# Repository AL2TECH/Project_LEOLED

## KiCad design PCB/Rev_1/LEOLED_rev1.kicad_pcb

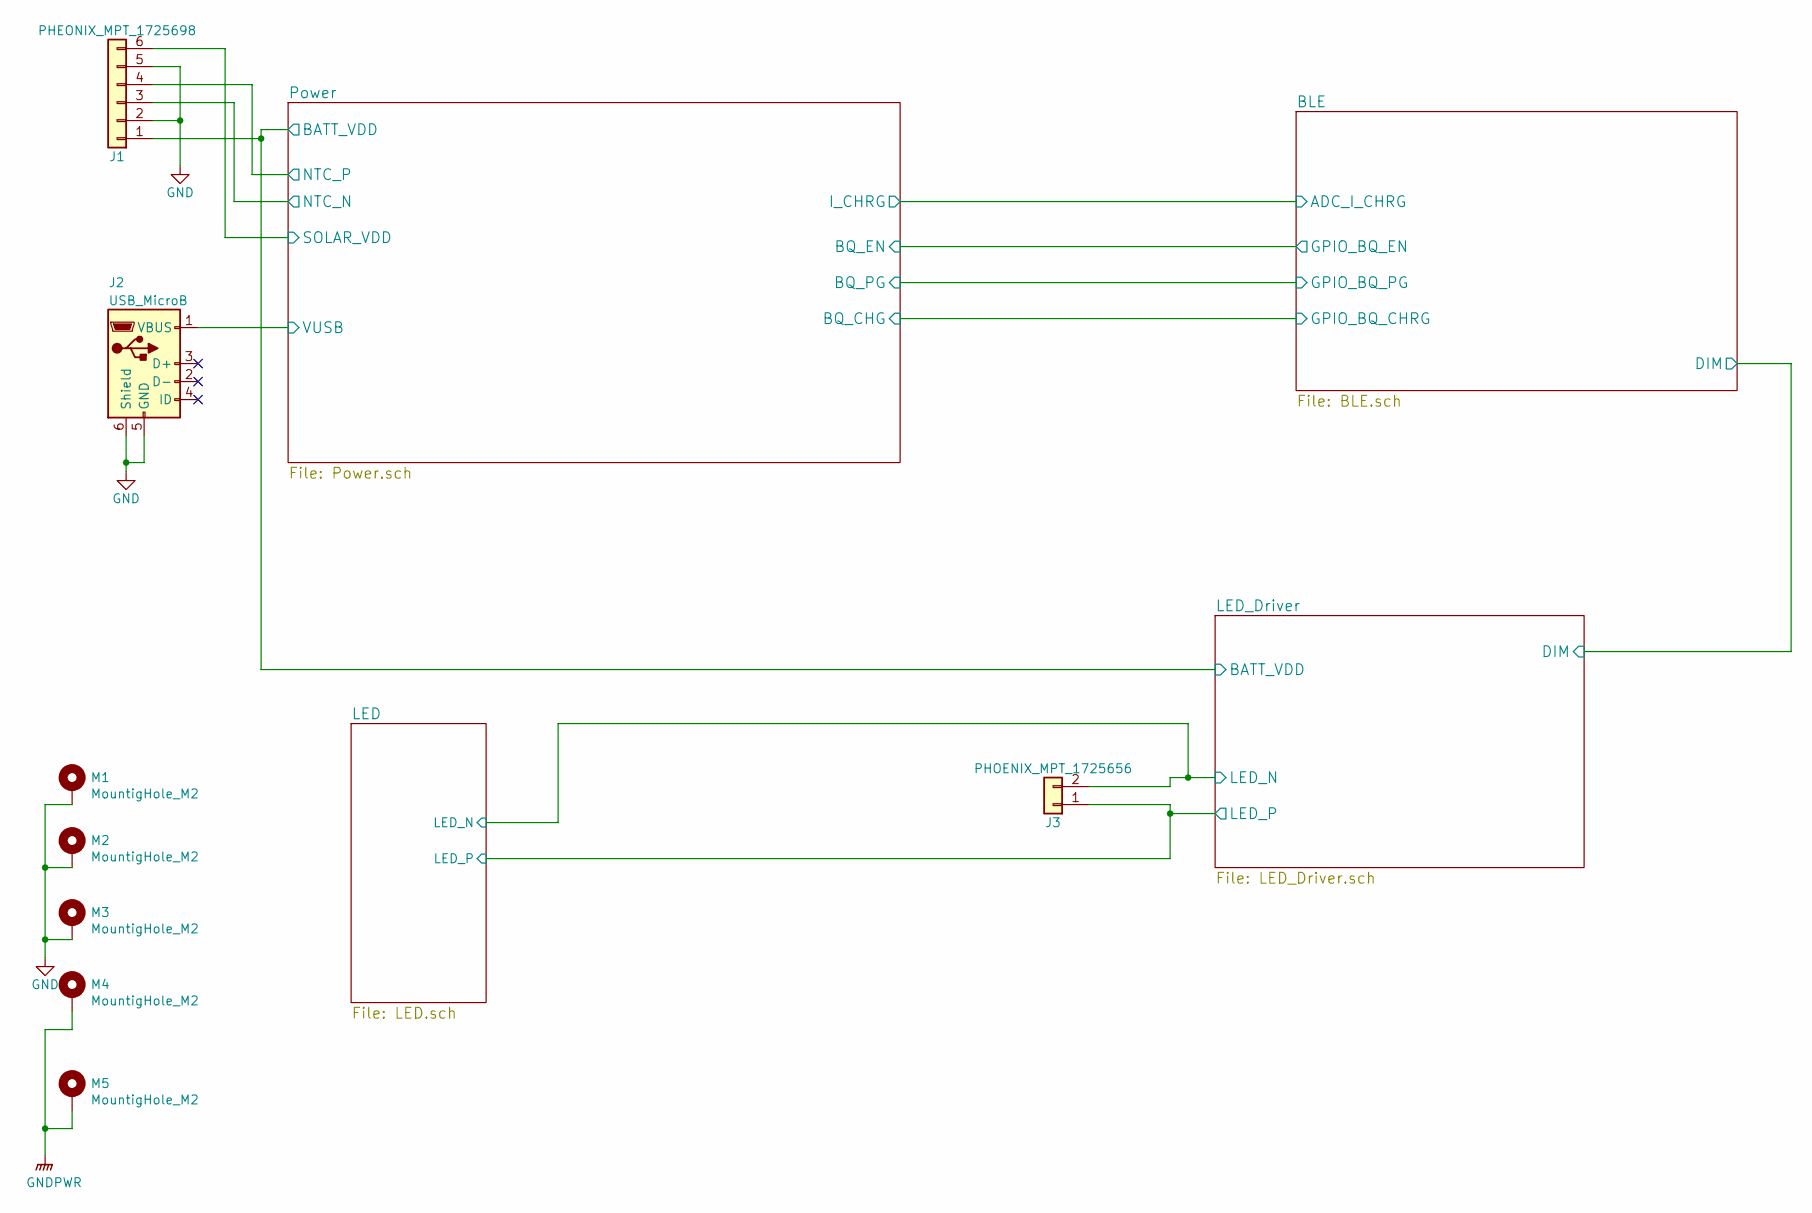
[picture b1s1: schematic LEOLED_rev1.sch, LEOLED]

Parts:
J1: PHEONIX_MPT_1725698; TerminalBlock_Pheonix_MPT-2.54mm_6pol; Rating 125V, 6A; Tolerance NA; Manufacturer PN 1725698
J2: USB_MicroB; USB_Micro-B_Molex-105017-0001; Rating NA; Tolerance NA; Manufacturer PN 1050170001
J3: PHOENIX_MPT_1725656; TerminalBlock_Pheonix_MPT-2.54mm_2pol; Rating 6A, 125V; Tolerance NA; Manufacturer PN 1725656
M1, M2, M3, M4, M5: MountigHole_M2; MountingHole_2.2mm_M2_ISO7380_Pad; Rating NA; Tolerance NA; Manufacturer PN NA

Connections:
/LED/LED_N: J3.2; also elsewhere on the board
/LED/LED_P: J3.1; also elsewhere on the board
/LED_Driver/BATT_VDD: J1.1; also elsewhere on the board
/Power/NTC_N: J1.3; also elsewhere on the board
/Power/NTC_P: J1.4; also elsewhere on the board
/Power/SOLAR_VDD: J1.6; also elsewhere on the board
/Power/VUSB: J2.1 (VBUS); also elsewhere on the board
GND: J1.2, J1.5, J2.5 (GND), J2.6 (Shield), M1.1, M2.1, M3.1; also elsewhere on the board
GNDPWR: M4.1, M5.1; also elsewhere on the board

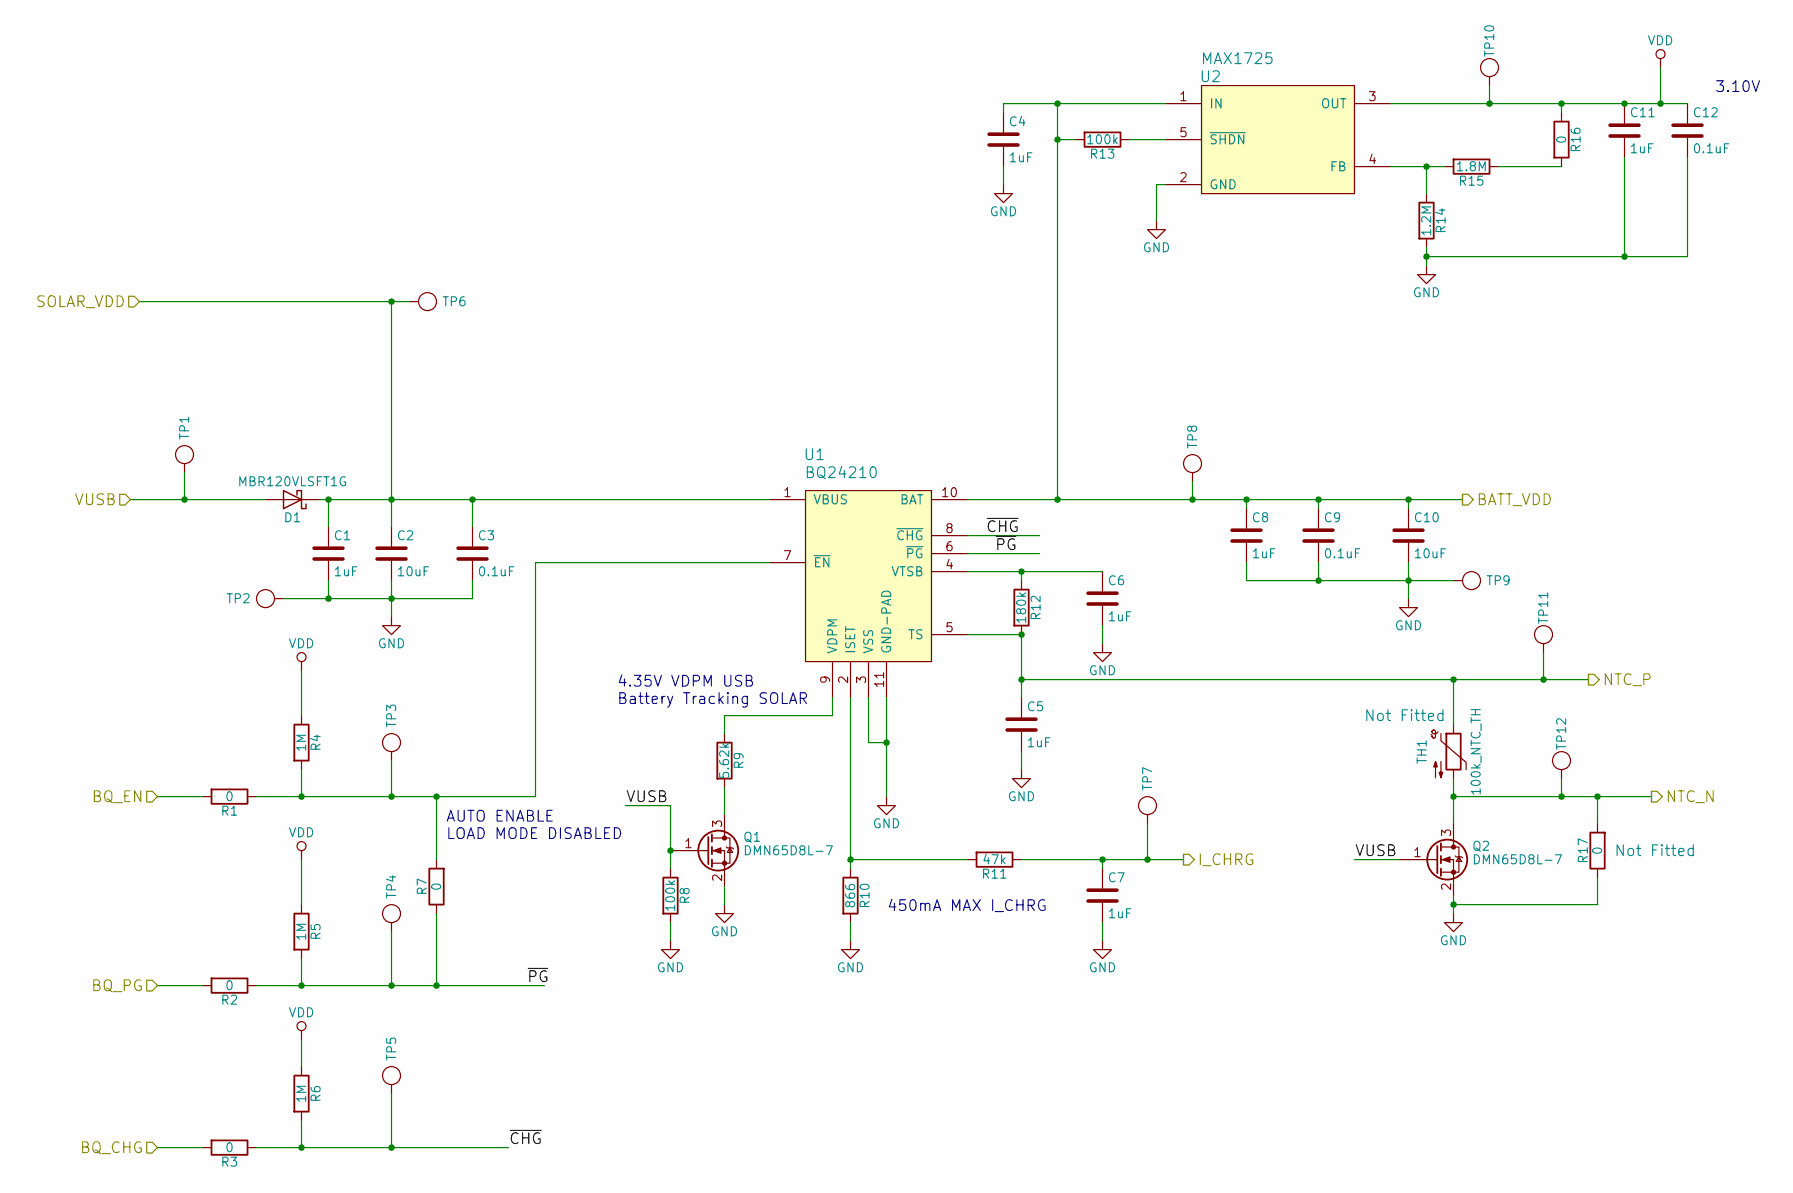
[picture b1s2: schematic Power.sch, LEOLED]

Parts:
C1, C4, C5, C6, C7, C8, C11: 1uF; C_0603_1608Metric; Rating 16V; Tolerance 20% X7R; Manufacturer PN GRM188R71C105MA12D
C2, C10: 10uF; C_1206_3216Metric; Rating 16V; Tolerance 10% X7R; Manufacturer PN CL31B106KOHZW6E
C3, C9, C12: 0.1uF; C_0603_1608Metric; Rating 16V; Tolerance 10% X7R; Manufacturer PN GRM188R71C104KA01D
D1: MBR120VLSFT1G; D_SOD-123FL; Rating 20V, 1A; Tolerance NA; Manufacturer PN MBR120VLSFT1G
Q1, Q2: DMN65D8L-7; SOT-23; Rating 60V, 310mA; Tolerance NA; Manufacturer PN DMN65D8L-7
R1, R2, R3, R7, R16, R17: 0; R_0603_1608Metric; Rating 0.1W; Tolerance 1%; Manufacturer PN CRG0603ZR
R4, R5, R6: 1M; R_0603_1608Metric; Rating 0.1W; Tolerance 1%; Manufacturer PN CRG0603F1M0
R8, R13: 100k; R_0603_1608Metric; Rating 0.1W; Tolerance 1%; Manufacturer PN CRG0603F100K
R9: 5.62k; R_0603_1608Metric; Rating 0.1W; Tolerance 1%; Manufacturer PN ERJ-3EKF5621V
R10: 866; R_0603_1608Metric; Rating 0.1W; Tolerance 1%; Manufacturer PN ERJ-3EKF8660V
R11: 47k; R_0603_1608Metric; Rating 0.1W; Tolerance 1%; Manufacturer PN CRCW060347K0FKEAC
R12: 180k; R_0603_1608Metric; Rating 0.1W; Tolerance 1%; Manufacturer PN CRCW0603180KFKEA
R14: 1.2M; R_0603_1608Metric; Rating 0.1W; Tolerance 1%; Manufacturer PN RC0603FR-071M2L
R15: 1.8M; R_0603_1608Metric; Rating 0.1W; Tolerance 1%; Manufacturer PN RC0603FR-071M8L
TH1: 100k_NTC_TH; R_0603_1608Metric; Rating NA; Tolerance 1%; Manufacturer PN NTCG164KF104FT1
TP1, TP2, TP3, TP4, TP5, TP6, TP7, TP8, TP9, TP10, TP11, TP12: Test_Point; TestPoint_Pad_D1.5mm; Rating NA; Tolerance NA; Manufacturer PN NA
U1: BQ24210; WSON-10-1EP_2x3mm_Pitch0.5mm_ThermalVias; Rating 7V; Tolerance NA; Manufacturer PN BQ24210DQCT
U2: MAX1725; SOT-23-5; Rating 12V; Tolerance NA; Manufacturer PN MAX1725EUK+T

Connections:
/BLE/ADC_I_CHRG: C7.1, R11.1, TP7.1; also elsewhere on the board
/LED_Driver/BATT_VDD: C4.1, C8.1, C9.1, C10.1, R13.2, TP8.1, U1.10 (BAT), U2.1 (IN); also elsewhere on the board
/Power/BQ_CHG: R3.2; also elsewhere on the board
/Power/BQ_EN: R1.2; also elsewhere on the board
/Power/BQ_PG: R2.2; also elsewhere on the board
/Power/NTC_N: Q2.3 (D), R17.2, TH1.2, TP12.1; also elsewhere on the board
/Power/NTC_P: C5.1, R12.2, TH1.1, TP11.1, U1.5 (TS); also elsewhere on the board
/Power/SOLAR_VDD: C1.1, C2.1, C3.1, D1.1 (K), TP6.1, U1.1 (VBUS); also elsewhere on the board
/Power/VUSB: D1.2 (A), Q1.1 (G), Q2.1 (G), R8.1, TP1.1; also elsewhere on the board
/Power/~CHG: R3.1, R6.2, TP5.1, U1.8 (~CHG)
/Power/~PG: R2.1, R5.2, R7.1, TP4.1, U1.6 (~PG)
GND: C1.2, C2.2, C3.2, C4.2, C5.2, C6.2, C7.2, C8.2, C9.2, C10.2, C11.2, C12.2, Q1.2 (S), Q2.2 (S), R8.2, R10.2, R14.2, R17.1, TP2.1, TP9.1, U1.3 (VSS), U1.11 (GND-PAD), U2.2 (GND); also elsewhere on the board
unnamed: C6.1, R12.1, U1.4 (VTSB)
unnamed: Q1.3 (D), R9.2
unnamed: R1.1, R4.2, R7.2, TP3.1, U1.7 (~EN)
unnamed: R9.1, U1.9 (VDPM)
unnamed: R10.1, R11.2, U1.2 (ISET)
unnamed: R13.1, U2.5 (~SHDN)
unnamed: R14.1, R15.2, U2.4 (FB)
unnamed: R15.1, R16.2
VDD: C11.1, C12.1, R4.1, R5.1, R6.1, R16.1, TP10.1, U2.3 (OUT); also elsewhere on the board

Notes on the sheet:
450mA MAX I_CHRG
4.35V VDPM USB Battery Tracking SOLAR
AUTO ENABLE LOAD MODE DISABLED
3.10V

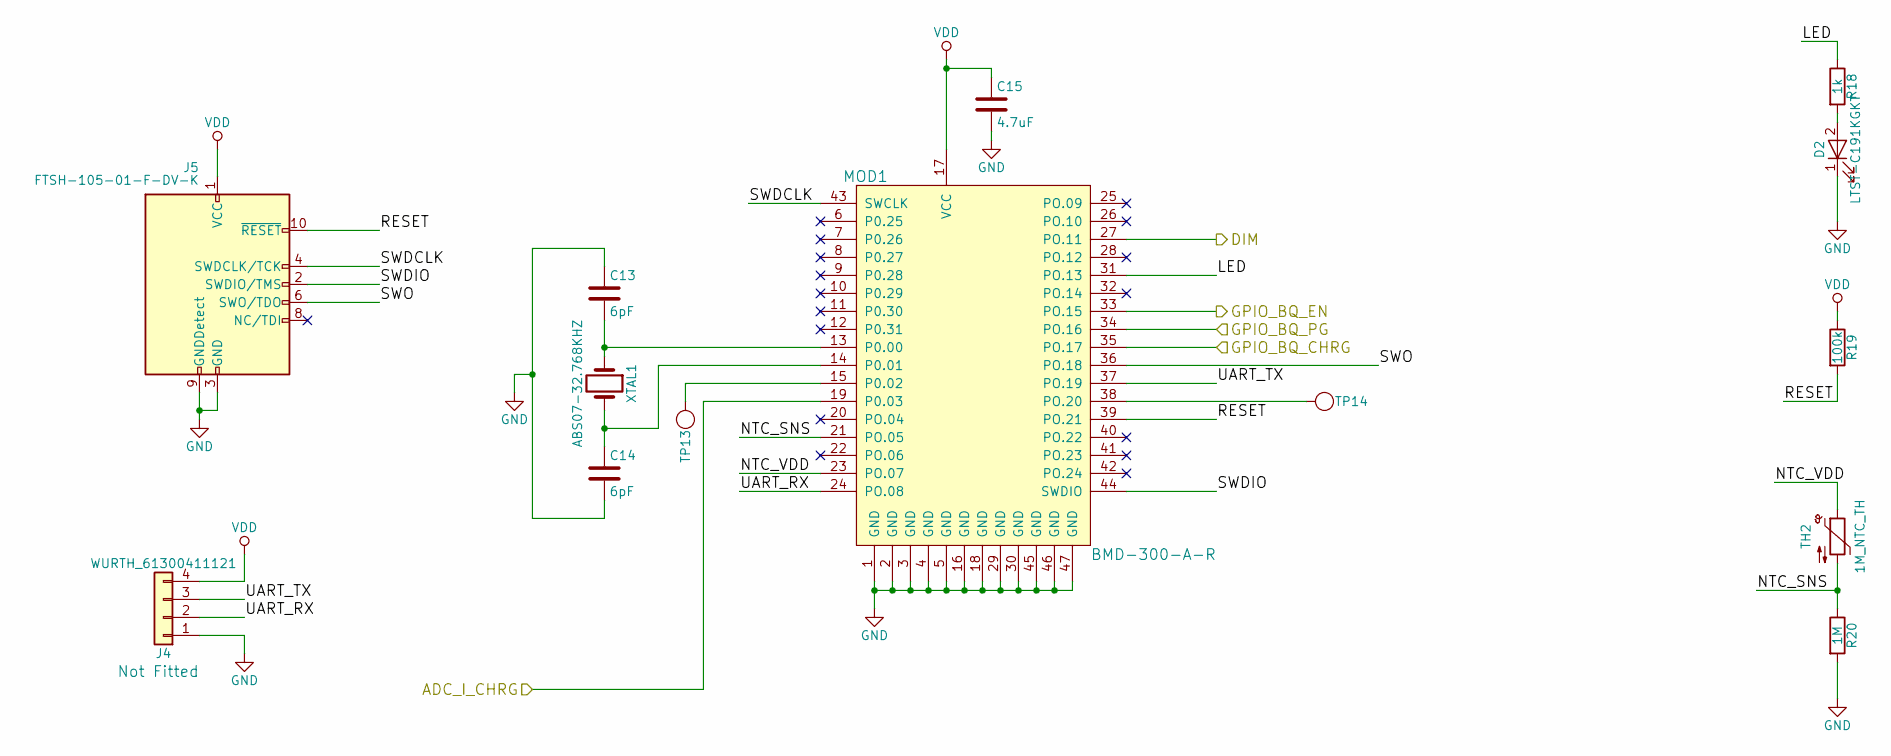
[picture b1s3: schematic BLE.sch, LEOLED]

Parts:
C13, C14: 6pF; C_0402_1005Metric; Rating 50V; Tolerance ±0.5pF; Manufacturer PN GRM1555C1H6R0DA01D
C15: 4.7uF; C_0603_1608Metric; Rating 16V; Tolerance 10% X5R; Manufacturer PN CL10A475KO8NNNC
D2: LTST-C191KGKT; LED_0603_1608Metric; Rating 20mA; Tolerance NA; Manufacturer PN LTST-C191KGKT
J4: WURTH_61300411121; Pin_Header_Straight_1x04_Pitch2.54mm; Rating NA; Tolerance NA; Manufacturer PN 61300411121
J5: FTSH-105-01-F-DV-K; Pin_Header_Straight_2x05_Pitch1.27mm_SMD; Rating NA; Tolerance NA; Manufacturer PN FTSH-105-01-F-DV-K
MOD1: BMD-300-A-R; BLE_Rigado_BMD-300; Rating 1.7V to 3V; Tolerance NA; Manufacturer PN BMD-300-A-R
R18: 1k; R_0603_1608Metric; Rating 0.1W; Tolerance 1%; Manufacturer PN CRG0603F1K0
R19: 100k; R_0603_1608Metric; Rating 0.1W; Tolerance 1%; Manufacturer PN CRG0603F100K
R20: 1M; R_0603_1608Metric; Rating 0.1W; Tolerance 1%; Manufacturer PN CRG0603F1M0
TH2: 1M_NTC_TH; R_0603_1608Metric; Rating 0.1W; Tolerance 3%, B25/50 4661K; Manufacturer PN NTCG164QH105HT1
TP13, TP14: Test_Point; TestPoint_Pad_D1.5mm; Rating NA; Tolerance NA; Manufacturer PN NA
XTAL1: ABS07-32.768KHZ; ABS07-32.768KHZ-7-T; Rating NA; Tolerance 20ppm; Manufacturer PN ABS07-32.768KHZ-7-T

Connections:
/BLE/ADC_I_CHRG: MOD1.19 (P0.03); also elsewhere on the board
/BLE/DIM: MOD1.27 (PO.11); also elsewhere on the board
/BLE/LED: MOD1.31 (PO.13), R18.1
/BLE/NTC_SNS: MOD1.21 (PO.05), R20.1, TH2.2
/BLE/NTC_VDD: MOD1.23 (PO.07), TH2.1
/BLE/RESET: J5.10 (~RESET~), MOD1.39 (PO.21), R19.2
/BLE/SWDCLK: J5.4 (SWDCLK/TCK), MOD1.43 (SWCLK)
/BLE/SWDIO: J5.2 (SWDIO/TMS), MOD1.44 (SWDIO)
/BLE/SWO: J5.6 (SWO/TDO), MOD1.36 (PO.18)
/BLE/UART_RX: J4.2, MOD1.24 (PO.08)
/BLE/UART_TX: J4.3, MOD1.37 (PO.19)
/Power/BQ_CHG: MOD1.35 (PO.17); also elsewhere on the board
/Power/BQ_EN: MOD1.33 (PO.15); also elsewhere on the board
/Power/BQ_PG: MOD1.34 (PO.16); also elsewhere on the board
GND: C13.1, C14.2, C15.2, D2.1 (K), J4.1, J5.3 (GND), J5.5 (GND), J5.9 (GNDDetect), MOD1.1 (GND), MOD1.2 (GND), MOD1.3 (GND), MOD1.4 (GND), MOD1.5 (GND), MOD1.16 (GND), MOD1.18 (GND), MOD1.29 (GND), MOD1.30 (GND), MOD1.45 (GND), MOD1.46 (GND), MOD1.47 (GND), R20.2; also elsewhere on the board
unnamed: C13.2, MOD1.13 (P0.00), XTAL1.1
unnamed: C14.1, MOD1.14 (P0.01), XTAL1.2
unnamed: D2.2 (A), R18.2
unnamed: MOD1.15 (P0.02), TP13.1
unnamed: MOD1.38 (PO.20), TP14.1
VDD: C15.1, J4.4, J5.1 (VCC), MOD1.17 (VCC), R19.1; also elsewhere on the board

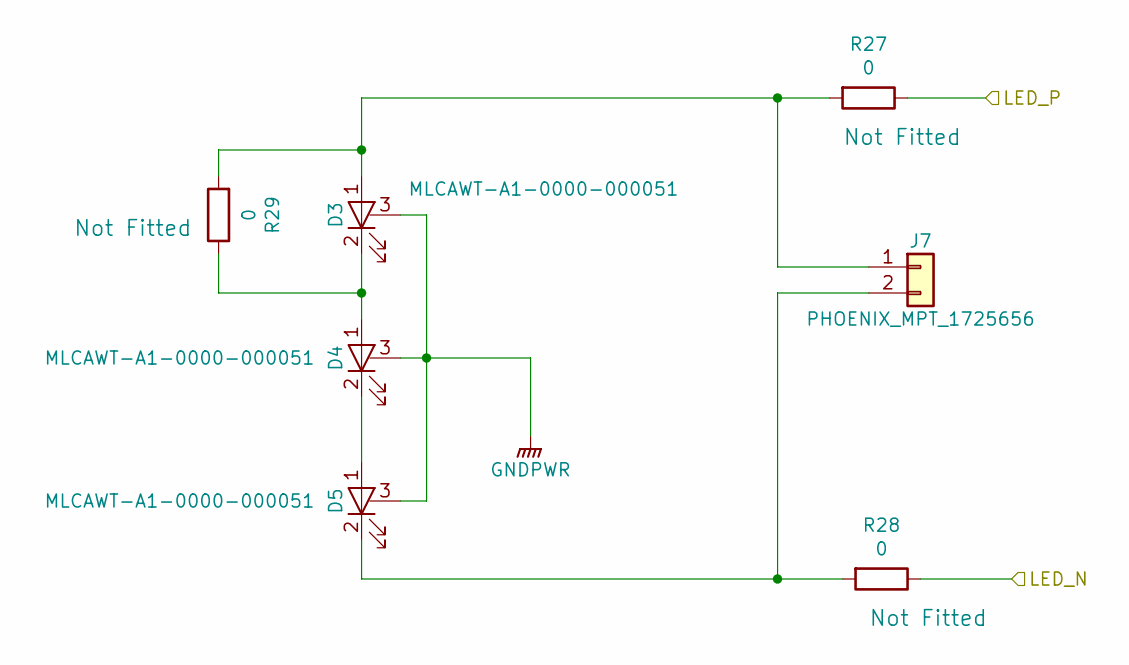
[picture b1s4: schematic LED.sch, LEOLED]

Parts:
D3, D4, D5: MLCAWT-A1-0000-000051; Cree_MLC; Rating 300mW; Tolerance NA; Manufacturer PN MLCAWT-A1-0000-000051
J7: PHOENIX_MPT_1725656; TerminalBlock_Pheonix_MPT-2.54mm_2pol; Rating 6A, 125V; Tolerance NA; Manufacturer PN 1725656
R27, R28, R29: 0; R_0805_2012Metric; Rating 0.125W; Tolerance NA; Manufacturer PN ERJ-6GEY0R00V

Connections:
/LED/LED_N: R28.1; also elsewhere on the board
/LED/LED_P: R27.1; also elsewhere on the board
GNDPWR: D3.3 (HS), D4.3 (HS), D5.3 (HS); also elsewhere on the board
unnamed: D3.1 (A), J7.1, R27.2, R29.2
unnamed: D3.2 (K), D4.1 (A), R29.1
unnamed: D4.2 (K), D5.1 (A)
unnamed: D5.2 (K), J7.2, R28.2

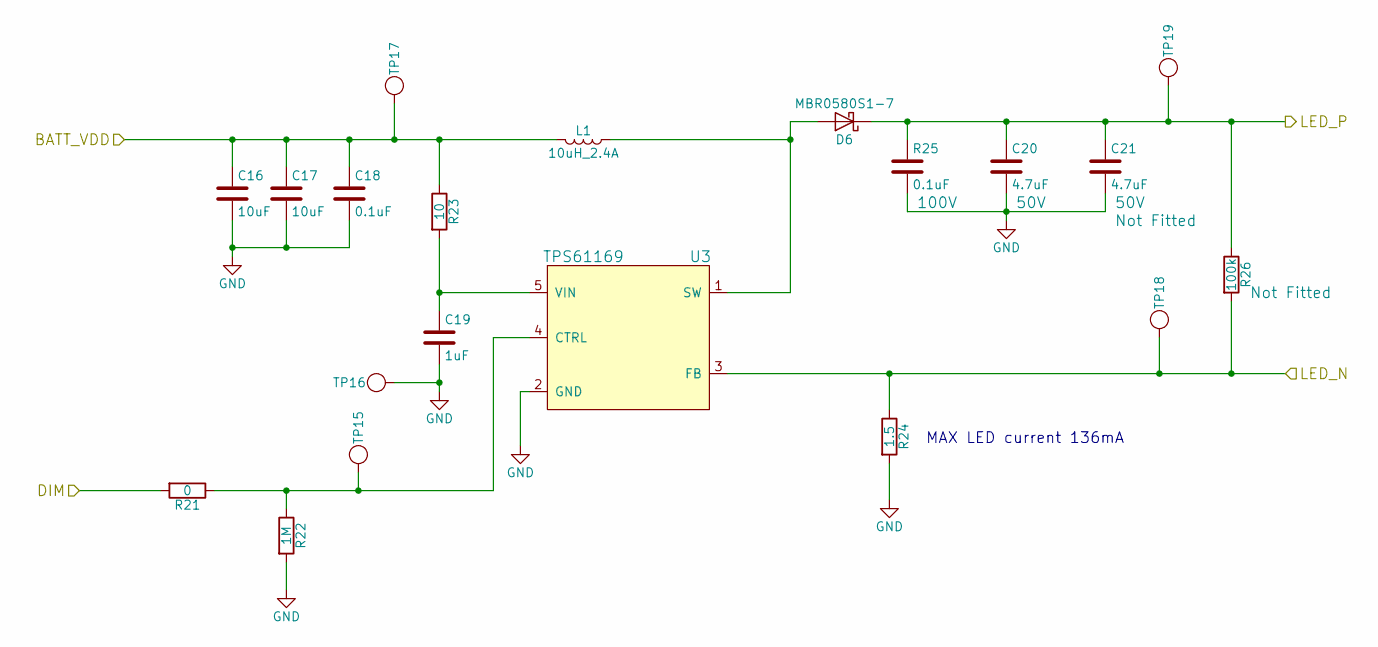
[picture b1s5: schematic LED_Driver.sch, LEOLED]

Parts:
C16, C17: 10uF; C_1206_3216Metric; Rating 16V; Tolerance 10% X7R; Manufacturer PN CL31B106KOHZW6E
C18: 0.1uF; C_0603_1608Metric; Rating 16V; Tolerance 10% X7R; Manufacturer PN GRM188R71C104KA01D
C19: 1uF; C_0603_1608Metric; Rating 16V; Tolerance 20% X7R; Manufacturer PN GRM188R71C105MA12D
C20, C21: 4.7uF; C_1206_3216Metric; Rating 50V; Tolerance X5R; Manufacturer PN CL31A475KB9LNNC
D6: MBR0580S1-7; D_SOD-123; Rating 500mA, 80V; Tolerance NA; Manufacturer PN MBR0580S1-7
L1: 10uH_2.4A; L_Wurth_5030; Rating 2.4A; Tolerance 20%; Manufacturer PN 74437336100
R21: 0; R_0603_1608Metric; Rating 0.1W; Tolerance 1%; Manufacturer PN CRG0603ZR
R22: 1M; R_0603_1608Metric; Rating 0.1W; Tolerance 1%; Manufacturer PN CRG0603F1M0
R23: 10; R_0603_1608Metric; Rating 0.1W; Tolerance 1%; Manufacturer PN AC0603FR-0710RL
R24: 1.5; R_0805_2012Metric; Rating 0.125W; Tolerance 1%; Manufacturer PN RC0805FR-071R5L
R25: 0.1uF; C_0805_2012Metric; Rating 100V; Tolerance 10%; Manufacturer PN GCM21BR72A104KA37L
R26: 100k; R_0603_1608Metric; Rating 0.1W; Tolerance 1%; Manufacturer PN CRG0603F100K
TP15, TP16, TP17, TP18, TP19: Test_Point; TestPoint_Pad_D1.5mm; Rating NA; Tolerance NA; Manufacturer PN NA
U3: TPS61169; TI_SC-70-5; Rating NA; Tolerance NA; Manufacturer PN TPS61169DCKR

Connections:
/BLE/DIM: R21.2; also elsewhere on the board
/LED/LED_N: R24.1, R26.2, TP18.1, U3.3 (FB); also elsewhere on the board
/LED/LED_P: C20.1, C21.1, D6.1 (K), R25.1, R26.1, TP19.1; also elsewhere on the board
/LED_Driver/BATT_VDD: C16.1, C17.1, C18.1, L1.2, R23.1, TP17.1; also elsewhere on the board
GND: C16.2, C17.2, C18.2, C19.2, C20.2, C21.2, R22.2, R24.2, R25.2, TP16.1, U3.2 (GND); also elsewhere on the board
unnamed: C19.1, R23.2, U3.5 (VIN)
unnamed: D6.2 (A), L1.1, U3.1 (SW)
unnamed: R21.1, R22.1, TP15.1, U3.4 (CTRL)

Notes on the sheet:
MAX LED current 136mA

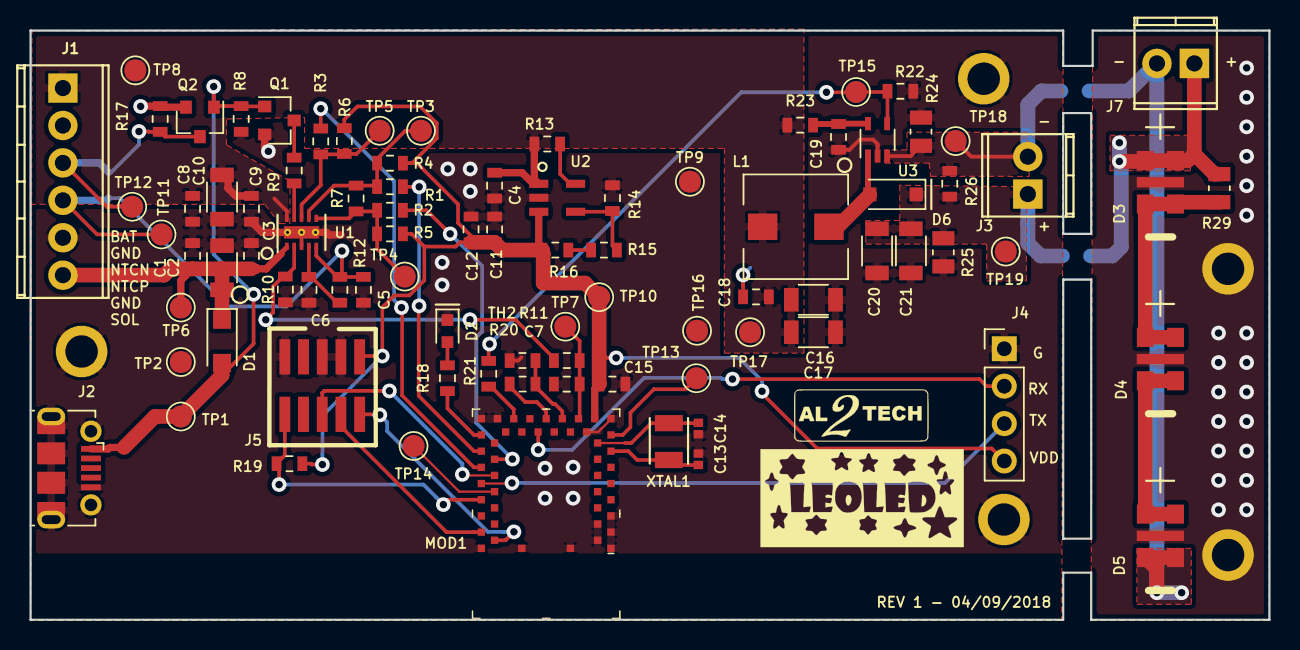
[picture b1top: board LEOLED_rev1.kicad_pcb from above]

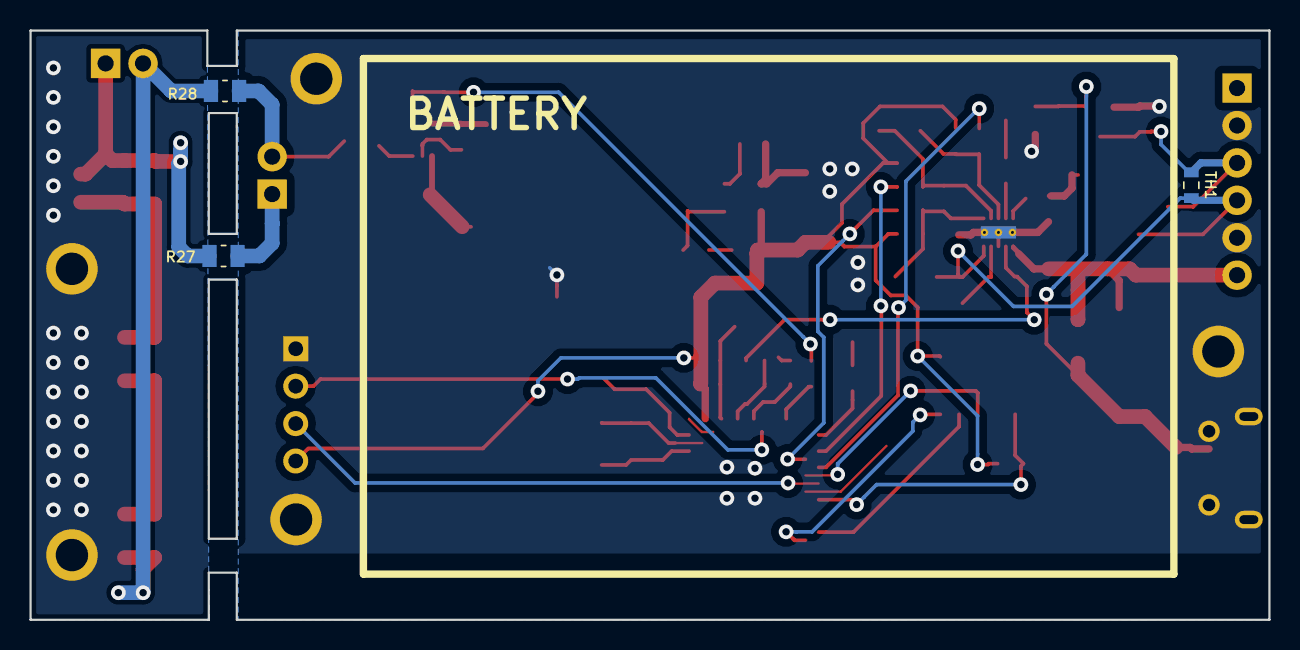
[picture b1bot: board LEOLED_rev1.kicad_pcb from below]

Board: 2 copper layers, 84.1 x 40.0 mm, 96 parts (3 on the bottom side), 46 nets.

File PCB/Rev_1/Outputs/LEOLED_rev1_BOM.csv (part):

"Source:","C:\Users\andrea.longobardi\OneDrive - maximintegrated.onmicrosoft.com\WORK\PERSONAL\AL2TECH\LEOLED\PCB\Rev_1\LEOLED_rev1.sch"
"Date:","6/25/2018 2:30:03 PM"
"Tool:","Eeschema (5.0.0-rc2-199-gf785d2749)"
"Generator:","C:\github_repo\Utilities\KiCad\KiCad_BOM_Generator/kicad_bom_generator.py"
"Component Count:","70"

"Individual Components:"

"Item","Qty","Reference(s)","Value","Description","Footprint","Datasheet","Rating","Tolerance","Manufacturer","Manufacturer PN","Supplier","Supplier PN","Supplier Link","Assembly Option"
"","","C1","1uF","	 1uF ±20% 16V Ceramic Capacitor X7R 0603 (1608 Metric)","Ceramic_Capacitor_SMD:C_0603_1608Metric","http://search.murata.co.jp/Ceramy/image/img/A01X/G101/ENG/GR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","16V","20% X7R ","Murata Electronics North America","GRM188R71C105MA12D","Digy-Key","490-6424-1-ND","https://www.digikey.com/product-detail/en/murata-electronics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","Fitted"
"","","C2","10uF","10µF ±10% 16V Ceramic Capacitor X7R 1206 (3216 Metric)","Ceramic_Capacitor_SMD:C_1206_3216Metric","http://www.samsungsem.com/kr/support/product-search/mlcc/CL3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","16V","10% X7R","Samsung Electro-Mechanics","CL31B106KOHZW6E","Digy-Key","1276-7032-1-ND","https://www.digikey.com/product-detail/en/samsung-electro-me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","Fitted"
"","","C3","0.1uF","	0.1uF ±10% 16V Ceramic Capacitor X7R 0603 (1608 Metric)","Ceramic_Capacitor_SMD:C_0603_1608Metric","http://search.murata.co.jp/Ceramy/image/img/A01X/G101/ENG/GR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","16V","10% X7R ","Murata Electronics North America","GRM188R71C104KA01D","Digy-Key","490-1532-1-ND","https://www.digikey.com/product-detail/en/murata-electronics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","Fitted"
"","","C4","1uF","	 1uF ±20% 16V Ceramic Capacitor X7R 0603 (1608 Metric)","Ceramic_Capacitor_SMD:C_0603_1608Metric","http://search.murata.co.jp/Ceramy/image/img/A01X/G101/ENG/GR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","16V","20% X7R ","Murata Electronics North America","GRM188R71C105MA12D","Digy-Key","490-6424-1-ND","https://www.digikey.com/product-detail/en/murata-electronics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","Fitted"
"","","C5","1uF","	 1uF ±20% 16V Ceramic Capacitor X7R 0603 (1608 Metric)","Ceramic_Capacitor_SMD:C_0603_1608Metric","http://search.murata.co.jp/Ceramy/image/img/A01X/G101/ENG/GR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","16V","20% X7R ","Murata Electronics North America","GRM188R71C105MA12D","Digy-Key","490-6424-1-ND","https://www.digikey.com/product-detail/en/murata-electronics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","Fitted"
"","","C6","1uF","	 1uF ±20% 16V Ceramic Capacitor X7R 0603 (1608 Metric)","Ceramic_Capacitor_SMD:C_0603_1608Metric","http://search.murata.co.jp/Ceramy/image/img/A01X/G101/ENG/GR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","16V","20% X7R ","Murata Electronics North America","GRM188R71C105MA12D","Digy-Key","490-6424-1-ND","https://www.digikey.com/product-detail/en/murata-electronics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","Fitted"
"","","C7","1uF","	 1uF ±20% 16V Ceramic Capacitor X7R 0603 (1608 Metric)","Ceramic_Capacitor_SMD:C_0603_1608Metric","http://search.murata.co.jp/Ceramy/image/img/A01X/G101/ENG/GR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","16V","20% X7R ","Murata Electronics North America","GRM188R71C105MA12D","Digy-Key","490-6424-1-ND","https://www.digikey.com/product-detail/en/murata-electronics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","Fitted"
"","","C8","1uF","	 1uF ±20% 16V Ceramic Capacitor X7R 0603 (1608 Metric)","Ceramic_Capacitor_SMD:C_0603_1608Metric","http://search.murata.co.jp/Ceramy/image/img/A01X/G101/ENG/GR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","16V","20% X7R ","Murata Electronics North America","GRM188R71C105MA12D","Digy-Key","490-6424-1-ND","https://www.digikey.com/product-detail/en/murata-electronics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","Fitted"
"","","C9","0.1uF","	0.1uF ±10% 16V Ceramic Capacitor X7R 0603 (1608 Metric)","Ceramic_Capacitor_SMD:C_0603_1608Metric","http://search.murata.co.jp/Ceramy/image/img/A01X/G101/ENG/GR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","16V","10% X7R ","Murata Electronics North America","GRM188R71C104KA01D","Digy-Key","490-1532-1-ND","https://www.digikey.com/product-detail/en/murata-electronics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","Fitted"
"","","C10","10uF","10µF ±10% 16V Ceramic Capacitor X7R 1206 (3216 Metric)","Ceramic_Capacitor_SMD:C_1206_3216Metric","http://www.samsungsem.com/kr/support/product-search/mlcc/CL3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","16V","10% X7R","Samsung Electro-Mechanics","CL31B106KOHZW6E","Digy-Key","1276-7032-1-ND","https://www.digikey.com/product-detail/en/samsung-electro-me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","Fitted"
"","","C11","1uF","	 1uF ±20% 16V Ceramic Capacitor X7R 0603 (1608 Metric)","Ceramic_Capacitor_SMD:C_0603_1608Metric","http://search.murata.co.jp/Ceramy/image/img/A01X/G101/ENG/GR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","16V","20% X7R ","Murata Electronics North America","GRM188R71C105MA12D","Digy-Key","490-6424-1-ND","https://www.digikey.com/product-detail/en/murata-electronics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","Fitted"
"","","C12","0.1uF","	0.1uF ±10% 16V Ceramic Capacitor X7R 0603 (1608 Metric)","Ceramic_Capacitor_SMD:C_0603_1608Metric","http://search.murata.co.jp/Ceramy/image/img/A01X/G101/ENG/GR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","16V","10% X7R ","Murata Electronics North America","GRM188R71C104KA01D","Digy-Key","490-1532-1-ND","https://www.digikey.com/product-detail/en/murata-electronics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","Fitted"
"","","C13","6pF","6pF ±0.5pF 50V Ceramic Capacitor C0G, NP0 0402","Ceramic_Capacitor_SMD:C_0402_1005Metric","http://search.murata.co.jp/Ceramy/image/img/A01X/G101/ENG/GR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","50V","±0.5pF","Murata Electronics North America","GRM1555C1H6R0DA01D","Digy-Key","490-5877-1-ND","https://www.digikey.com/products/en?keywords=490-5877-1-ND","Fitted"
"","","C14","6pF","6pF ±0.5pF 50V Ceramic Capacitor C0G, NP0 0402","Ceramic_Capacitor_SMD:C_0402_1005Metric","http://search.murata.co.jp/Ceramy/image/img/A01X/G101/ENG/GR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","50V","±0.5pF","Murata Electronics North America","GRM1555C1H6R0DA01D","Digy-Key","490-5877-1-ND","https://www.digikey.com/products/en?keywords=490-5877-1-ND","Fitted"
"","","C15","4.7uF","	 4.7uF ±10% 16V Ceramic Capacitor X5R 0603 (1608 Metric)","Ceramic_Capacitor_SMD:C_0603_1608Metric","http://www.samsungsem.com/kr/front/downloadcms.do?path=/kr/s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","16V","10% X5R","Samsung Electro-Mechanics","CL10A475KO8NNNC","Digy-Key","1276-1784-1-ND","https://www.digikey.com/product-detail/en/samsung-electro-me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","Fitted"
"","","C16","10uF","10µF ±10% 16V Ceramic Capacitor X7R 1206 (3216 Metric)","Ceramic_Capacitor_SMD:C_1206_3216Metric","http://www.samsungsem.com/kr/support/product-search/mlcc/CL3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","16V","10% X7R","Samsung Electro-Mechanics","CL31B106KOHZW6E","Digy-Key","1276-7032-1-ND","https://www.digikey.com/product-detail/en/samsung-electro-me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","Fitted"
"","","C17","10uF","10µF ±10% 16V Ceramic Capacitor X7R 1206 (3216 Metric)","Ceramic_Capacitor_SMD:C_1206_3216Metric","http://www.samsungsem.com/kr/support/product-search/mlcc/CL3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","16V","10% X7R","Samsung Electro-Mechanics","CL31B106KOHZW6E","Digy-Key","1276-7032-1-ND","https://www.digikey.com/product-detail/en/samsung-electro-me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","Fitted"
"","","C18","0.1uF","	0.1uF ±10% 16V Ceramic Capacitor X7R 0603 (1608 Metric)","Ceramic_Capacitor_SMD:C_0603_1608Metric","http://search.murata.co.jp/Ceramy/image/img/A01X/G101/ENG/GR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","16V","10% X7R ","Murata Electronics North America","GRM188R71C104KA01D","Digy-Key","490-1532-1-ND","https://www.digikey.com/product-detail/en/murata-electronics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","Fitted"
"","","C19","1uF","	 1uF ±20% 16V Ceramic Capacitor X7R 0603 (1608 Metric)","Ceramic_Capacitor_SMD:C_0603_1608Metric","http://search.murata.co.jp/Ceramy/image/img/A01X/G101/ENG/GR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","16V","20% X7R ","Murata Electronics North America","GRM188R71C105MA12D","Digy-Key","490-6424-1-ND","https://www.digikey.com/product-detail/en/murata-electronics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","Fitted"
"","","C20","4.7uF","4.7µF ±10% 50V Ceramic Capacitor X5R 1206 (3216 Metric)","Ceramic_Capacitor_SMD:C_1206_3216Metric","http://www.samsungsem.com/kr/support/product-search/mlcc/CL3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","50V","X5R","Samsung Electro-Mechanics","CL31A475KB9LNNC","Digy-Key","1276-2731-2-ND","https://www.digikey.com/product-detail/en/samsung-electro-me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","Fitted"
"","","C21","4.7uF","4.7µF ±10% 50V Ceramic Capacitor X5R 1206 (3216 Metric)","Ceramic_Capacitor_SMD:C_1206_3216Metric","http://www.samsungsem.com/kr/support/product-search/mlcc/CL3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","50V","X5R","Samsung Electro-Mechanics","CL31A475KB9LNNC","Digy-Key","1276-2731-2-ND","https://www.digikey.com/product-detail/en/samsung-electro-me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","Not Fitted"
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
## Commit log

2018-06-27 layout edit
2018-06-28 layout editing
2018-07-01 added assembly folder
2018-07-17 adding assembly folder
2018-08-09 generating output files
2018-08-09 removing backup file
2018-09-04 UART header not fitted
2018-10-19 Adding gerber job file and PDFs
2019-04-29 cleaning up
